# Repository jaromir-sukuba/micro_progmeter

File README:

repository for https://hackaday.io/project/7988-micro-progmeter
HW design files in cadsoft eagle 6 and higher

The whole project is licensed under MIT license, see LICENSE.md file.

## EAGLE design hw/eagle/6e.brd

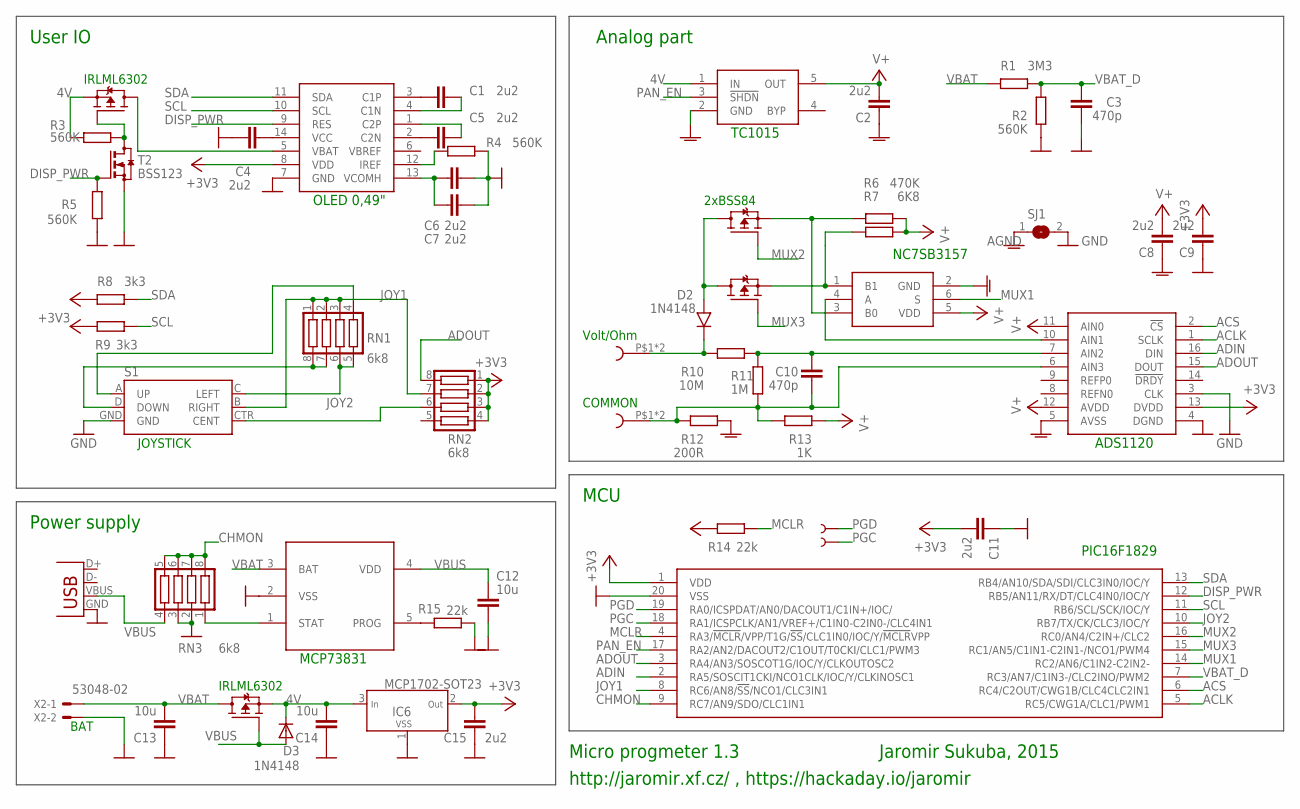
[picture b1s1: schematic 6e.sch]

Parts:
C1, C2, C4, C5, C6, C7, C8, C9, C11, C15: 2u2; 0603
C3, C10: 470p; 0603
C12, C13, C14: 10u; R0805
D1: DISP_OLED_049B; DISP_OLED_049_B
D2: 1N4148; SOD-80
D3: 1N4148; SOD123
IC1: TC1015; SOT23-5
IC2: NC7SB3157; SC70-6
IC3: ADS1120; TSSOP16
IC4: MCP73831; SOT23-5
IC5: PIC16F1508SSOP20; SSOP20
IC6: MCP1702-SOT23; SOT23
R1: 3M3; 0603
R2, R3, R4, R5: 560K; 0603
R6: 470K; R0805
R7: 6K8; R0805
R8, R9: 3k3; 0603
R10: 10M; R0805
R11: 1M; R0805
R12: 200R; 0603
R13: 1K; 0603
R14, R15: 22k; 0603
RN1, RN2, RN3: 6k8; CTS742C083
S1: JOYSTICK_MINI
SJ1: SJ
T1, T3, T4, T5: BSS84; SOT23-3
T2: BSS123; SOT23
TE1, TE2: BANPLUG_2
TP1, TP2: TEST-POINT3X5; PAD.03X.05
X1: USB-MICROB
X2: 53048-02

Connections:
4V: C14.2, D3.C, IC1.1 (IN), IC6.3 (IN), R3.1, T1.2 (S), T5.2 (S)
+3V3: C9.2, C11.2, C15.2, D1.8 (VDD), IC3.13 (DVDD), IC5.1 (VDD), IC6.2 (OUT), R8.2, R9.2, R14.2, RN2.1, RN2.2, RN2.3, RN2.4
ACLK: IC3.1 (SCLK), IC5.5 (RC5/CWG1A/CLC1/PWM1)
ACS: IC3.2 (!CS), IC5.6 (RC4/C2OUT/CWG1B/CLC4CLC2IN1)
ADIN: IC3.16 (DIN), IC5.2 (RA5/SOSCIT1CKI/NCO1CLK/IOC/Y/CLKINOSC1)
ADOUT: IC3.15 (DOUT), IC5.3 (RA4/AN3/SOSCOT1G/IOC/Y/CLKOUTOSC2), RN2.8
AGND: C2.1, C8.1, IC1.2 (GND), IC2.2 (GND), IC3.5 (AVSS), R12.1, SJ1.1
CHMON: IC5.9 (RC7/AN9/SDO/CLC1IN1), RN3.5, RN3.6, RN3.7, RN3.8
DISP_PWR: D1.9 (RES), IC5.12 (RB5/AN11/RX/DT/CLC4IN0/IOC/Y), R5.2, T2.1 (G)
GND: C3.1, C4.1, C6.2, C7.2, C9.1, C11.1, C12.2, C13.1, C14.1, C15.1, D1.7 (GND), IC3.3 (CLK), IC3.4 (DGND), IC4.2 (VSS), IC5.20 (VSS), IC6.1 (VSS), R2.2, R4.1, R5.1, R15.1, RN3.2, RN3.3, S1.GND, SJ1.2, T2.2 (S), X1.GND, X2.2
JOY1: IC5.8 (RC6/AN8/!SS!/NCO1/CLC3IN1), RN1.1, RN1.2, RN1.3, RN2.7, S1.B (RIGHT)
JOY2: IC5.10 (RB7/TX/CK/CLC3/IOC/Y), RN2.6, S1.CTR (CENT)
MCLR: IC5.4 (RA3/!MCLR!/VPP/T1G/!SS!/CLC1IN0/IOC/Y/!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), R14.1
MUX1: IC2.6 (S), IC5.14 (RC2/AN6/C1IN2-C2IN2-)
MUX2: IC5.16 (RC0/AN4/C2IN+/CLC2), T3.1 (G)
MUX3: IC5.15 (RC1/AN5/C1IN1-C2IN1-/NCO1/PWM4), T4.1 (G)
unnamed: IC2.1 (B1), R7.2, T4.2 (S)
unnamed: IC2.3 (B0), R6.2, T3.2 (S)
unnamed: IC2.4 (A), IC3.10 (AIN1)
unnamed: D2.K, R10.2, TE1.P$1, TE1.P$2
unnamed: R3.2, T1.1 (G), T2.3 (D)
unnamed: C10.2, IC3.7 (AIN2), R10.1, R11.1
unnamed: IC4.1 (STAT), RN3.1
unnamed: C10.1, IC3.6 (AIN3), R11.2, R12.2, R13.1, TE2.P$1, TE2.P$2
unnamed: C4.2, D1.14 (VCC)
unnamed: D1.5 (VBAT), T1.3 (D)
unnamed: C6.1, C7.1, D1.13 (VCOMH)
unnamed: D1.12 (IREF), R4.2
unnamed: D2.A, T3.3 (D), T4.3 (D)
unnamed: RN1.4, S1.A (UP)
unnamed: C1.1, D1.3 (C1P)
unnamed: C5.1, D1.2 (C2N)
unnamed: C5.2, D1.1 (C2P)
unnamed: C1.2, D1.4 (C1N)
unnamed: RN1.5, RN1.6, S1.C (LEFT)
unnamed: RN1.7, RN1.8, S1.D (DOWN)
unnamed: IC4.5 (PROG), R15.2
PAN_EN: IC1.3 (!SHDN), IC5.17 (RA2/AN2/DACOUT2/C1OUT/T0CKI/CLC1/PWM3)
PGC: IC5.18 (RA1/ICSPCLK/AN1/VREF+/C1IN0-C2IN0-/CLC4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), TP2.P$1
PGD: IC5.19 (RA0/ICSPDAT/AN0/DACOUT1/C1IN+/IOC/), TP1.P$1
SCL: D1.10 (SCL), IC5.11 (RB6/SCL/SCK/IOC/Y), R9.1
SDA: D1.11 (SDA), IC5.13 (RB4/AN10/SDA/SDI/CLC3IN0/IOC/Y), R8.1
V+: C2.2, C8.2, IC1.5 (OUT), IC2.5 (VDD), IC3.11 (AIN0), IC3.12 (AVDD), R6.1, R7.1, R13.2
VBAT: C13.2, IC4.3 (BAT), R1.2, T5.3 (D), X2.1
VBAT_D: C3.2, IC5.7 (RC3/AN7/C1IN3-/CLC2INO/PWM2), R1.1, R2.1
VBUS: C12.1, D3.A, IC4.4 (VDD), RN3.4, T5.1 (G), X1.VBUS

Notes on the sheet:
BAT
Micro progmeter 1.3
Jaromir Sukuba, 2015
http://jaromir.xf.cz/ , https://hackaday.io/jaromir
User IO
Analog part
Power supply
MCU
ADS1120
OLED 0,49"
MCP73831
TC1015
PIC16F1829
NC7SB3157
Volt/Ohm
COMMON
2xBSS84
JOYSTICK
IRLML6302

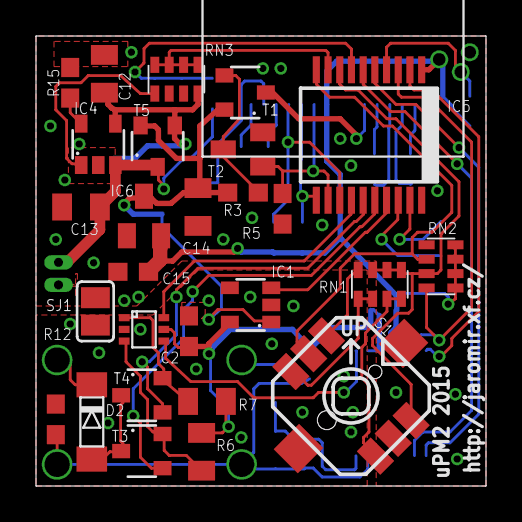
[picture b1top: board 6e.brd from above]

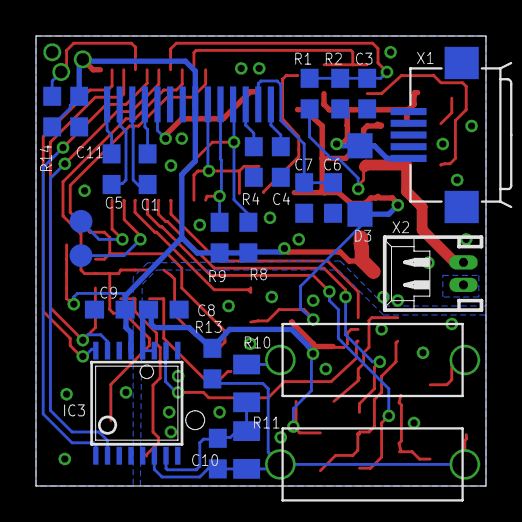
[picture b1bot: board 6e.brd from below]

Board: 2 copper layers, 25.0 x 25.0 mm, 55 parts (27 on the bottom side), 46 nets.

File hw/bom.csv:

"Qty";"Value";"Device";"Package";"Parts";"Description";"";
"1";"";"DIODE-SOD123";"SOD123";"D3";"DIODE";"";
"1";"";"JOYSTICK_MINI";"JOYSTICK_MINI";"S1";"Small 5-way tactile joystick, COM-10063";"";
"1";"";"SJ";"SJ";"SJ1";"SMD solder JUMPER";"";
"1";"0R";"R_0603";"0603";"R12";"";"";
"1";"10K";"R_0805";"R0805";"R7";"";"";
"1";"10M";"R_0805";"R0805";"R10";"";"";
"3";"10u";"C_0806";"R0805";"C12, C13, C14";"";"";
"1";"1M";"R_0805";"R0805";"R11";"";"";
"1";"1N4148";"1N4148SOD";"SOD-80";"D2";"";"";
"2";"22k";"R_0603";"0603";"R14, R15";"";"";
"10";"2u2";"C_0603";"0603";"C1, C2, C4, C5, C6, C7, C8, C9, C11, C15";"";"";
"1";"3M3";"R_0603";"0603";"R1";"";"";
"2";"3k3";"R_0603";"0603";"R8, R9";"";"";
"1";"470K";"R_0805";"R0805";"R6";"";"";
"2";"470p";"C_0603";"0603";"C3, C10";"";"";
"1";"53048-02";"53048-02";"53048-02";"X2";"CONNECTOR";"";
"3";"560K";"R_0603";"0603";"R2, R3, R5";"";"";
"1";"560k";"R_0603";"0603";"R4";"";"";
"3";"6k8";"CTS742C083";"CTS742C083";"RN1, RN2, RN3";"Chip Resistor Array 4 Single Resistor";"";
"1";"ADS1120";"ADS1120";"TSSOP16";"IC3";"";"";
"2";"BANPLUG_2";"BANPLUG_2";"BANPLUG_2";"U$1, U$2";"";"BANANA PLUG 2mm";
"1";"BSS123";"BSS123";"SOT23";"T2";"N-CHANNEL MOS FET";"";
"4";"BSS84";"BSS84";"SOT23-3";"T1, T3, T4, T5";"";"";
"1";"DISP_OLED_049B";"DISP_OLED_049B";"DISP_OLED_049_B";"D1";"";"";
"1";"DNP";"R_0603";"0603";"R13";"";"";
"1";"MCP1702-SOT23";"MCP1702-SOT23";"SOT23";"IC5";"";"";
"1";"MCP73831";"MCP73831";"SOT23-5";"U$3";"";"";
"1";"NC7SB3157";"NC7SB3157";"SC70-6";"IC2";"";"";
"1";"PIC16F1508SSOP20";"PIC16F1508SSOP20";"SSOP20";"IC4";"";"";
"1";"TC1015";"TC1015";"SOT23-5";"IC1";"";"";
"2";"TEST-POINT3X5";"TEST-POINT3X5";"PAD.03X.05";"TP1, TP2";"";"";
"1";"USB-MICROB";"USB-MICROB";"USB-MICROB";"X1";"USB Connectors";"";

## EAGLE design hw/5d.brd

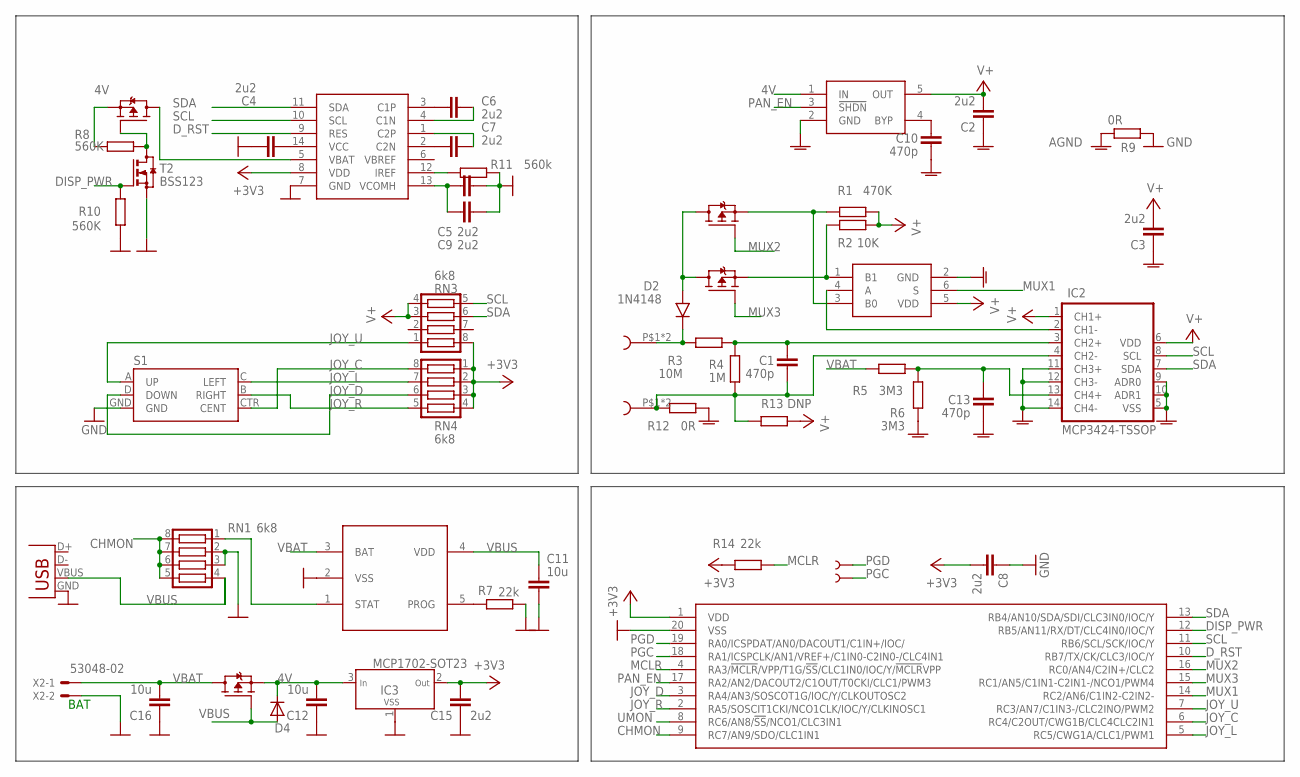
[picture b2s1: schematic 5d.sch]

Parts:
C1, C10, C13: 470p; 0603
C2, C3, C4, C5, C6, C7, C8, C9, C15: 2u2; 0603
C11, C12, C16: 10u; R0805
D1: DISP_OLED_049B; DISP_OLED_049_B
D2: 1N4148; SOD-80
D4: DIODE-SOD123; SOD123
IC2: MCP3424-TSSOP; TSSOP14
IC3: MCP1702-SOT23; SOT23
IC5: NC7SB3157; SC70-6
R1: 470K; R0805
R2: 10K; R0805
R3: 10M; R0805
R4: 1M; R0805
R5, R6: 3M3; 0603
R7, R14: 22k; 0603
R8, R10: 560K; 0603
R9, R12: 0R; 0603
R11: 560k; 0603
R13: DNP; 0603
RN1, RN3, RN4: 6k8; CTS742C083
S1: JOYSTICK_MINI
T1, T3, T4, T5: BSS84; SOT23-3
T2: BSS123; SOT23
TP1, TP2: TEST-POINT3X5; PAD.03X.05
U$1, U$2: BANPLUG_2
U$3: TC1015; SOT23-5
U$4: MCP73831; SOT23-5
U$6: PIC16F1508SSOP20; SSOP20
X1: USB-MICROB
X2: 53048-02

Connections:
4V: C12.2, D4.C, IC3.3 (IN), R8.1, T1.2 (S), T3.2 (S), U$3.1 (IN)
+3V3: C8.2, C15.2, D1.8 (VDD), IC3.2 (OUT), R14.2, RN3.8, RN4.1, RN4.2, RN4.3, RN4.4, U$6.1 (VDD)
AGND: C2.1, C3.1, C10.1, C13.1, IC2.5 (VSS), IC2.9 (ADR0), IC2.10 (ADR1), IC2.11 (CH3+), IC2.12 (CH3-), IC2.14 (CH4-), IC5.2 (GND), R6.2, R9.1, R12.1, U$3.2 (GND)
CHMON: RN1.5, RN1.6, RN1.7, RN1.8, U$6.9 (RC7/AN9/SDO/CLC1IN1)
DISP_PWR: R10.2, T2.1 (G), U$6.12 (RB5/AN11/RX/DT/CLC4IN0/IOC/Y)
D_RST: D1.9 (RES), U$6.10 (RB7/TX/CK/CLC3/IOC/Y)
GND: C4.1, C5.2, C8.1, C9.2, C11.2, C12.1, C15.1, C16.1, D1.7 (GND), IC3.1 (VSS), R7.1, R9.2, R10.1, R11.1, RN1.2, RN1.3, S1.GND, T2.2 (S), U$4.2 (VSS), U$6.20 (VSS), X1.GND, X2.2
JOY_C: RN4.8, S1.CTR (CENT), U$6.6 (RC4/C2OUT/CWG1B/CLC4CLC2IN1)
JOY_D: RN4.6, S1.D (DOWN), U$6.3 (RA4/AN3/SOSCOT1G/IOC/Y/CLKOUTOSC2)
JOY_L: RN4.7, S1.C (LEFT), U$6.5 (RC5/CWG1A/CLC1/PWM1)
JOY_R: RN4.5, S1.B (RIGHT), U$6.2 (RA5/SOSCIT1CKI/NCO1CLK/IOC/Y/CLKINOSC1)
JOY_U: RN3.1, S1.A (UP), U$6.7 (RC3/AN7/C1IN3-/CLC2INO/PWM2)
MCLR: R14.1, U$6.4 (RA3/!MCLR!/VPP/T1G/!SS!/CLC1IN0/IOC/Y/!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)
MUX1: IC5.6 (S), U$6.14 (RC2/AN6/C1IN2-C2IN2-)
MUX2: T4.1 (G), U$6.16 (RC0/AN4/C2IN+/CLC2)
MUX3: T5.1 (G), U$6.15 (RC1/AN5/C1IN1-C2IN1-/NCO1/PWM4)
unnamed: C10.2, U$3.4 (BYP)
unnamed: IC5.1 (B1), R2.2, T5.2 (S)
unnamed: IC5.3 (B0), R1.2, T4.2 (S)
unnamed: C13.2, IC2.13 (CH4+), R5.1, R6.1
unnamed: IC2.2 (CH1-), IC5.4 (A)
unnamed: D2.K, R3.2, U$1.P$1, U$1.P$2
unnamed: R8.2, T2.3 (D), T3.1 (G)
unnamed: C1.2, IC2.3 (CH2+), R3.1, R4.1
unnamed: RN1.1, U$4.1 (STAT)
unnamed: C1.1, IC2.4 (CH2-), R4.2, R12.2, R13.1, U$2.P$1, U$2.P$2
unnamed: C4.2, D1.14 (VCC)
unnamed: D1.5 (VBAT), T3.3 (D)
unnamed: C5.1, C9.1, D1.13 (VCOMH)
unnamed: D1.12 (IREF), R11.2
unnamed: D2.A, T4.3 (D), T5.3 (D)
unnamed: C6.1, D1.3 (C1P)
unnamed: C7.1, D1.2 (C2N)
unnamed: C7.2, D1.1 (C2P)
unnamed: C6.2, D1.4 (C1N)
unnamed: R7.2, U$4.5 (PROG)
PAN_EN: U$3.3 (!SHDN), U$6.17 (RA2/AN2/DACOUT2/C1OUT/T0CKI/CLC1/PWM3)
PGC: TP2.P$1, U$6.18 (RA1/ICSPCLK/AN1/VREF+/C1IN0-C2IN0-/CLC4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)
PGD: TP1.P$1, U$6.19 (RA0/ICSPDAT/AN0/DACOUT1/C1IN+/IOC/)
SCL: D1.10 (SCL), IC2.8 (SCL), RN3.5, U$6.11 (RB6/SCL/SCK/IOC/Y)
SDA: D1.11 (SDA), IC2.7 (SDA), RN3.6, U$6.13 (RB4/AN10/SDA/SDI/CLC3IN0/IOC/Y)
UMON: U$6.8 (RC6/AN8/!SS!/NCO1/CLC3IN1)
V+: C2.2, C3.2, IC2.1 (CH1+), IC2.6 (VDD), IC5.5 (VDD), R1.1, R2.1, R13.2, RN3.3, RN3.4, U$3.5 (OUT)
VBAT: C16.2, R5.2, T1.3 (D), U$4.3 (BAT), X2.1
VBUS: C11.1, D4.A, RN1.4, T1.1 (G), U$4.4 (VDD), X1.VBUS

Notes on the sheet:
BAT

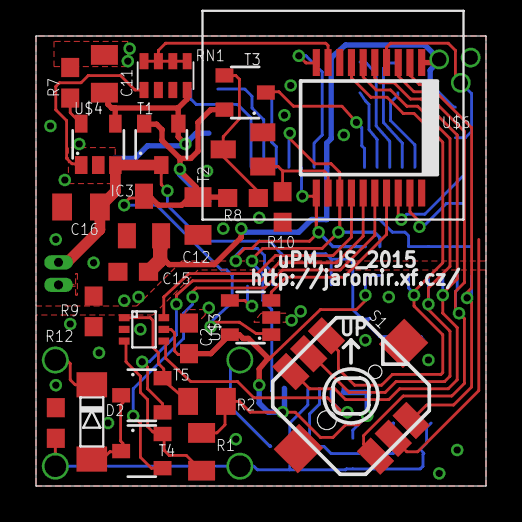
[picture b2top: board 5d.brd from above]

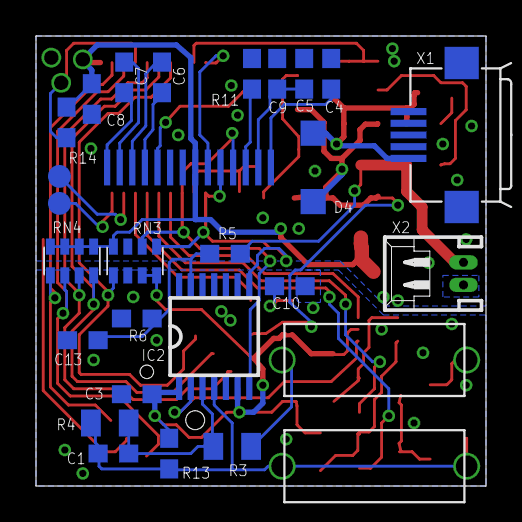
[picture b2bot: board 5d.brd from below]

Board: 2 copper layers, 25.0 x 25.0 mm, 53 parts (27 on the bottom side), 44 nets.

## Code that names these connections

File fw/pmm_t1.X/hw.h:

//this is where compilers switching occurs
#ifdef __XC8 
#define	COMPILER_XC8
#endif
#ifndef __XC8 
#define	COMPILER_SDCC
#endif


#define CAL_COEF_A -0.00040
#define CAL_COEF_B -0.00466
#define CAL_COEF_C  0.0230


#define	_XTAL_FREQ	(2000000*1)
#define	IIC_BAUD	100
#define	SSP_BRG		((_XTAL_FREQ/4000)/IIC_BAUD)-1


#ifdef  COMPILER_SDCC
//********************************************************************************************************************
// a lot of defines fot SDCC compiler
//********************************************************************************************************************
#include "pic16f1829.h"

#define mTIMER_F_CLR TMR0IF = 0
#define mGET_ADC        ((((unsigned int)(ADRESH))<<8)|ADRESL)

#define ADC_DELAY __asm__ ("nop");

#define	DISP_PWR	 LATB5
#define	DISP_PWR_T	 TRISB5
#define	PAN_EN		 LATA2
#define	PAN_EN_T	 TRISA2

#define	ADC_CS		 LATC4
#define	ADC_CS_T	 TRISC4
#define	ADC_CLK		 LATC5
#define	ADC_CLK_T	 TRISC5
#define	ADC_DI		 LATA5
#define	ADC_DI_T	 TRISA5
#define	ADC_DO		 LATA4
#define	ADC_DO_I	 RA4
#define	ADC_DO_T	 TRISA4

#define	MUX2		 LATC0
#define	MUX2_T		 TRISC0
#define	MUX3		 LATC1
#define	MUX3_T		 TRISC1
#define	MUX1		 LATC2
#define	MUX1_T		 TRISC2

#define SSP_SEN     SEN
#define SSP_PEN     PEN
#define SSP_IF      SSP1IF
#define SSP_RSEN    RSEN
#define SSP_BUF     SSPBUF
#define SSP_RCEN    RCEN
#define SSP_ACKDT   ACKDT
#define SSP_ACKEN   ACKEN

#define JOY_BTN_M   RB7

#define ICD_PGD_T     TRISA0
#define ICD_PGC_T     TRISA1

#define mSLEEP      __asm__ ("sleep");
#define mRESET      __asm__ ("reset");

#elif defined (COMPILER_XC8)
//********************************************************************************************************************
// a lot of defines fot XC8 compiler
//********************************************************************************************************************
#include <xc.h>

#define mTIMER_F_CLR INTCONbits.TMR0IF = 0
#define mGET_ADC        ((((unsigned int)(ADRESH))<<8)|ADRESL)

#define ADC_DELAY   __delay_us(1)

#define	DISP_PWR	LATBbits.LATB5
#define	DISP_PWR_T	TRISBbits.TRISB5
#define	PAN_EN		LATAbits.LATA2
#define	PAN_EN_T	TRISAbits.TRISA2

#define	ADC_CS		LATCbits.LATC4
#define	ADC_CS_T	TRISCbits.TRISC4
#define	ADC_CLK		LATCbits.LATC5
#define	ADC_CLK_T	TRISCbits.TRISC5
#define	ADC_DI		LATAbits.LATA5
#define	ADC_DI_T	TRISAbits.TRISA5
#define	ADC_DO		LATAbits.LATA4
#define	ADC_DO_I	PORTAbits.RA4
#define	ADC_DO_T	TRISAbits.TRISA4

#define	MUX2		LATCbits.LATC0
#define	MUX2_T		TRISCbits.TRISC0
#define	MUX3		LATCbits.LATC1
#define	MUX3_T		TRISCbits.TRISC1
#define	MUX1		LATCbits.LATC2
#define	MUX1_T		TRISCbits.TRISC2

#define SSP_SEN     SSP1CON2bits.SEN
#define SSP_PEN     SSP1CON2bits.PEN
#define SSP_IF      SSP1IF
#define SSP_RSEN    SSP1CON2bits.RSEN
#define SSP_BUF     SSPBUF
#define SSP_RCEN    SSP1CON2bits.RCEN
#define SSP_ACKDT   SSP1CON2bits.ACKDT
#define SSP_ACKEN   SSP1CON2bits.ACKEN

#define JOY_BTN_M   PORTBbits.RB7

#define ICD_PGD_T     TRISAbits.TRISA0
#define ICD_PGC_T     TRISAbits.TRISA1

#define mSLEEP      asm("sleep");
#define mRESET      asm("reset");

#endif




//********************************************************************************************************************
//********************************************************************************************************************
//generic defines for both compilers
//********************************************************************************************************************
//********************************************************************************************************************

#define JOY_N   0
#define JOY_U   1
#define JOY_D   2
#define JOY_R   3
#define JOY_L   4
#define JOY_M   5



void hw_init (void);
void iic_start (void);
void iic_start_addr (unsigned char address);
void iic_stop (void);
void iic_rstart (void);
void iic_write (unsigned char data);
unsigned char iic_read (unsigned char ack);
void dly_ms(unsigned int i);
unsigned char adc_setup (unsigned char res, unsigned char chnl);
unsigned int adc_get_data (unsigned char channel, unsigned char gain);
unsigned char adc_spi (unsigned char data);
void adc_write_reg (unsigned char addr, unsigned char data);
unsigned char adc_read_reg (unsigned char addr);
void meter_res_range (unsigned char range);


void shdn (void);

void start_adc (unsigned char chnl);
unsigned int get_adc (void);

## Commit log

2015-10-08 :lollipop: Added .gitattributes
2015-10-08 hardware rev 1
2015-10-08 hw rev 1 pdf
2015-10-09 PCB ver 1.1
    minor cleanup
2015-12-01 gerber data
    gerber data
2015-12-02 files cleanup
    files cleanup
2015-12-07 bom, version 1
    bom, version 1
2015-12-07 bom, version 2
    bom, version 2
2015-12-07 BOM updated to correct CSV
    BOM updated to correct CSV
2015-12-08 firmware rev. 1
    firmware rev. 1
2015-12-09 testing release
    testing release
2015-12-16 firmware rev 2, mechanical files
    firmware rev 2, mechanical files
2015-12-16 BOM 2
    BOM 2
2015-12-16 BOM 2
    BOM2
2015-12-16 BOM2
    BOM2
2015-12-16 schematics cleanup, bom update
    schematics cleanup, bom update
2015-12-16 BOM update
    BOM update
2015-12-16 schematics cleanup
    schematics cleanup
2015-12-22 final release
    final release
2015-12-22 final BOM
    final BOM
2015-12-23 calibration coefficients update
    calibration coefficients update
2015-12-25 BOM update
    changed PIC16F1508 to 16LF1829
2016-01-07 MIT licensing update
    MIT licensing update

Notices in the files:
parts and their libraries:
SparkFun-Electromechanical: Licensing: CC v3.0 Share-Alike You are welcome to use this library for commercial purposes.
